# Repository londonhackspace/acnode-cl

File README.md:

Table of Contents
=================

  * [Table of Contents](#table-of-contents)
  * [Features](#features)
  * [Parts list](#parts-list)
    * [For the transistor switch](#for-the-transistor-switch)
    * [For the rest of the node:](#for-the-rest-of-the-node)
    * [Making the transistor switch](#making-the-transistor-switch)
    * [Wiring in the arcade switch](#wiring-in-the-arcade-switch)
    * [How to get this running with a cooqrobot/elechouse pn532 breakout board:](#how-to-get-this-running-with-a-cooqrobotelechouse-pn532-breakout-board)
    * [Using the tool running pin](#using-the-tool-running-pin)
  * [Building and flashing the firmware](#building-and-flashing-the-firmware)
  * [Pin assignments:](#pin-assignments)
  * [using the CLI](#using-the-cli)
  * [Roles](#roles)
  * [Button status/colours:](#button-statuscolours)
  * [To use the button menu:](#to-use-the-button-menu)
    * [For maintainers the menu items are:](#for-maintainers-the-menu-items-are)
    * [So for a user to take a tool out of service:](#so-for-a-user-to-take-a-tool-out-of-service)
    * [For a maintainer to access the menu and do nothing:](#for-a-maintainer-to-access-the-menu-and-do-nothing)
    * [For a maintainer to add a card:](#for-a-maintainer-to-add-a-card)
  * [Glossary](#glossary)
    * [Offline and Online](#offline-and-online)
    * [In service and Out of service](#in-service-and-out-of-service)

# Features

* Command line interface for settings over the usb port

* Stores settings in EEPROM

* Can log to a syslog server

* Uses DHCP to get it's IP address

* Optional pin to detect when a tool is running - good for detecting when consumables are being used

* Can record the total runtime of of the tool if the tool running pin is used.

* Button with RGB led for status.

* Single Button menu for adding cards and putting a tool off and online.

* Can cache 752 cards to the embedded eeprom.

# Parts list

## For the transistor switch

* 1 x NPN transistor, i used a 2N3904
* 1 x 1K resistor
* 1 x small bit (8 x 8 holes is fine) of Vero board
* 2 x C shaped crimp or solderable terminals for the relay
* 2 x wires with female header socket ends (the other end doesn't matter, and will be cut off), one black, and one red.
* 1 x black female to female header socket lead
* 1 x grey female to female header socket lead

## For the rest of the node:

* 2 x crimp or solderable spade terminals for the microswitch on the arcade button
* 2 x wires with female header socket ends (the other end doesn't matter, and will be cut off), one black & one white
* 1 x PN532 based card reader
* 1 x connected Launchpad TM4C1294XL
* 1 x red  female to female header socket lead
* 1 x blue female to female header socket lead
* 1 x green female to female header socket lead
* 1 x black female to female header socket lead

##  Making the transistor switch

* cut one end off the 2 wires with header socket ends, leaving as much wire
as possible and the female ends

* Strip the bare end crimp into the terminals - for the arcade button
terminals use a white and black wire, and for the relay use red and black
wires.

* Attach the red wire to the+ side of the VDC connections on the SSR and the
black one to the - side.

* Attach the red female and to +5v header pin on the launchpad

* On some strip board solder the transistor on one edge with the flat side
facing the rest of the board.

* Cut the track connected to the middle (base) pin of the transistor in the
middle of the board

* Solder the 1K resistor over the hole you've cut

* Solder a 3 pin header so the middle pin goes header -> 1k resistor ->
middle (base) of the transistor, and the left and right pins are connected
to the left and right pin of the transistor

Picture of stripboard + transistor + header:

https://pointless.net/photos/id/1419346624/

Picture of the bottom showing cut track:

https://pointless.net/photos/id/1419346632/

* with the header pins towards you looking edge on at the board (the flat
side of the transistor should be facing you), the pins are, from left to
right:

* 1 connect to GND on the connected launchpad with a black female to female lead.
* 2 connect to PG_1 on the connected launchpad
* 3 connect to - on the ssr VDC side with the black lead you made earlier

## Wiring in the arcade switch

* make two spade terminal leads, one white and one black

like this:

https://pointless.net/photos/id/1419334749/

* connect the black one to the bottom of the microswitch on the button and the other end to a convenient GND on the launchpad

* connect the white end to the terminal labelled "NO" on the microswitch, and the other end to PF_1 on the launchpad

* connect the white lead of the RGB led leads to +5V on the launchpad

* the RGB red, green and blue leads go to PM0, PM1 and PM2

## How to get this running with a cooqrobot/elechouse pn532 breakout board:

1. Cooqrobot boards: Carefully unsolder the 0 ohm resistor jumper from the HIS0 connector, then resolder it (or just bridge the pads with solder) so that the '0' side is connected rather than the 1, this puts the reader in HSU mode.
  Elechouse boards: Set the DIP switches both to the right (This is as shipped from the factory) to put the reader into HSU mode.

2. Solder headers onto the 8 pin connector on the board where the TX/RX pins are, you need at least TX,RX,5V,GND. N.B. Cooqrobot boards: you can't use the SCL/SDA pins on the 4 pin connector because they have pullups on them...

2. Connect 5v and GND to somewhere convenient on the connected launchpad

4. This sketch uses Serial6 which uses PP0 and PP1, AKA pins 43 and 44 on the connected launchpad, connect those too, PP0 goes to TX on the board and PP1 to RX.

5. Check the labels on the card reader boards carefully, one cheap reader board has the pins for the FTDI cable pinouts *backwards* on the top (component) side of the board. Also some card readers label TX and RX the other way round... Do not use cheap Elechouse NFC Reader V3 clones - they often have the wrong component values in their antenna matching stage, and cannot energise cards well. Genuine Elechouse NFC Reader V4 (Direct from Elechouse, work well, the extra price is worth it for avoiding the hassle of deploying an under-performing reader).

See here for the Connected Launchpad pinouts:

http://energia.nu/pin-maps/guide_tm4c129launchpad/

## Using the tool running pin

You can send a signal to the acnode via pin PE_4 to say when your tool is actually running (as opposed to being switched on), useful for keeping track of wear and tear and consumables etc.

# Building and flashing the firmware

(non-PlatformIO version, tested on MacOS 10.12.6, 10.14.4 and Ubuntu 18.04)

* Install git for your platform if you haven't already
* Install cmake for your platform (http://cmake.org , debian/ubuntu package: cmake, MacOS homebrew: `brew install cmake`)
* Create a build directory
```
mkdir build
```
* Run the shell script
```
./gettoolchain.sh
````
* Update/initialise the git submodules
```
git submodule update --init
```
* Use cmake to make a Makefile, and define your target board (EK-TM4C1294XL)
  ```
  cd build && cmake .. -DCMAKE_TOOLCHAIN_FILE=../targets/tivac-launchpad/EK-TM4C1294XL.cmake
  ```
    * If building on MacOS, you may need to put the cmake binary on your path if you downloaded it manually or refer to it as
  /Applications/CMake.app/Contents/bin/cmake
* Use Gnu make to actually run the dependencies, compile and link:
```
make -j
```
* When ready to upload the resultant elf binary to the Launchpad,
```
make -j flash
```

# Pin assignments:

* PG_1 - active high, switches power to the tool, output
* PF_1 - the button, active low (uses internal pullup), input
* PM_0 - RGB button Red channel, output
* PM_1 - RGB button Green channel, output
* PM_2 - RGB button Blue channel, output
* PP_0 - Serial RX from the card reader, input (should connect to TX on the card reader)
* PP_1 - Serial TX to the card reader, output (should connect to RX on the card reader)
* PE_4 - tool running pin, active low (uses internal pullup), input
* PD_0 - SD Card MISO (pin 7) aka D0
* PD_1 - SD Card MOSI (pin 2) aka CMD
* PD_3 - SD card clock (pin 5)
* PC_7 - SD card CS (pin 1) aka CD

# Pin assignments on ACNode shield rev 1 board (square PCB)

Other ACnode PCBs are available, the most common at the moment is the hardware/NEW-ACNode-Dootbot-Shield designed by dawidekziaja

* P1 connector (numbers rising towards on-board relay, P1_1 is furthest from it)
* P1_1 GND -> CAT5 ORANGE
* P1_2 +3.3V    NOT CONNECTED
* P1_3 PP0 RX ->  CAT5 WHITE/GREEN -> PN532 TXD
* P1_4 PP1 TX -> CAT5 GREEN -> PN532 RXD

* P3 connector (numbers rising towards reset button)
* P3_1 +3.3V
* P3_2 Red LED -> CAT5 BLUE
* P3_3 Green LED -> CAT5 WHITE/BROWN
* P3_4 Blue LED -> CAT5 BROWN

* P4 connector (numbers rising away from reset button)
* P4_1 +5V -> CAT5 WHITE/ORANGE
* P4_2 
* P4_3 GND

Button connector / Doorbell or ACnode menu button
* PF_1 SWITCH -> CAT5 WHTE/BLUE
* GND 

Door release button
* PM6 SWITCH -> Normally Open
* GND

* Note that Deek-Robot and Elechouse branded PN532 boards need +5V not +3.3v to function. 
Use the pinouts labelled on the back of the board.
Other boards (Genuine Elechouse NFC module v3) sort of work at +3.3V, but may not give sufficient juice to the NFC target to energise certain types of cards.

# Reader installation

For convenience of installation (acnode), and added security (doorbot), we recommend the reader module itself should be connected via an 8 wire cable, such as CAT5, and housed with a push-button NO switch and RGB LED in its own enclosure. This way, any intruder can't attack the reader and easily gain access. CAT5 (or above) wiring as above. Note the requirement for 220 ohm resistors on the Red/Green/Blue LED pins to prevent LED burnout. For operational convenience, it is advised to keep a spare reader that can be swapped out. Readers for doorbot enclosures can fit into standard single EN 60670-1 socket boxes with blanking plates, or outdoor junction boxes. For outdoor fitting, ensure that any holes for the button are suitably sealed against moisture ingress. Ditto for ACnode readers in a dusty or dirty environment. 

# Common reader enclosures

## ACnode role
Schneider Electric P/N SL00925 100x100x500 junction box smooth walls has been used for ACnode enclosures in the past. (Farnell DPN10/10 161706)
[ Internal free space 80x80x35mm to brim, there's 10mm outside of this area, compromised by the  mounting posts for the cover ]
[ Cover free space 80x80x16mm to brim, there's 10mm outside of this area, compromised by the mounting posts for the cover ]
Arcade Button with 5V Common Cathode RGB LED, from https://www.arcadeworlduk.com/, e.g. Ultralux RGB Illuminated Arcade Button, mounting hole required 28mm diameter hole in side of enclosure.
Mount PN532 reader and breakout board on the lid
(Optional - use RJ45 modular jack on the side of the enclosure and run a small patch lead to the breakout board, or find a suitable way of terminating the CAT5). Ideally, the readers are easily swappable between ACnodes, so mod jack on the side is a good plan.
Mount modular jack on opposite side of enclosure box to arcade button.

## Internal doorbot role

BS EN 60670-1 45mm deep single socket box with blanking plate
5V Common Cathode RGB LED
N/O SPST push button for doorbell. Choose one that doesn't accidentally get triggered while swiping.
Mount PN532 reader and breakout board on the blanking plate. Wire RJ45 CAT5 cable within walls.
## External doorbot role

British General WPJBS IP55 external junction box from B&Q
[ Internal free space 50x60x35mm, 8mm outide this space, compromised by the mounting posts for the cover ]
5V Common Cathode RGB LED
N/O SPST push button, *water resistant*. Choose one that doesn't accidentally get triggered while swiping.
Run CAT5 cable through a sealed grommet on the rear through the wall.

Pin Assignments
* +5V : RJ45_1 : WHITE/ORANGE : +5V
* GND : RJ45_2 : ORANGE : GND
* PP_0 : RJ45_3 : WHITE/GREEN : -> PN532 TXD
* PM_0 : RJ45_4 : BLUE : VIA R220 - RGB RED 
* PF_1 : RJ45_5 : WHITE/BLUE : the button, active low (uses internal pullup), input
* PP_1 : RJ45_6 : GREEN : PN532 RXD
* PM_1 : RJ45_7 : WHITE/BROWN : VIA R220 - RGB Green
* PM_2 : RJ45_8 : BROWN : VIA R220 - RGB BLUE

# Power supply

For ACnodes, then a Power over Ethernet micro-USB power splitter works a treat. Feed the 5V USB power straight to the OTG micro USB connector near the ethernet jack, and jumper the Power Select to OTG. Make sure you connect to a network port that is supplied via a PoE network switch.
For doorbots, you will need +12V to power the door solenoid, and ideally, a battery backup. Feed the +12V into the London Hackspace doorbot board so that it goes via a regulator to supply +5V to the Launchpad via the BoosterPack connector. Jumper the launchpad's Power Select to OTG.

# using the CLI

Once the firmware has been uploaded to the connected launchpad connect with a serial terminal (if you use a real one rather than the Energia serial monitor you get command history and line editing).
It will work a lot better if it's connected to a working ethernet port with DHCP at this point.

Use `help` to see a brief description of commands. You want to set the nodeid and toolname as the minimum:

```
nodeid <id>
name <name of tool>
server <acserver hostname>
port <http port to use>
secret <shared secret, see acserver tool config>
syslog <syslog server to use>
mqtt_topic_base <mqtt_topic_base e.g. /tool/selfclearingdesk >
maintainercache - toggle maintainer cache mode (stores maintainers credentials in EEPROM so it should still work for maintainers after complete power loss)
```

and then `save` to save the settings.

It is good practice to make a note of the MAC address of the acnode, and reserve a DHCP reservation on the router for it, because then it can be monitored by icinga or other monitoring system.

# Button status/colours:

* Starting up: rainbow cycling
* In service, idle: blue
* In service, valid user, tool on: green
* In service, invalid user: red
* In service, maintainer: yellow
* Out of service, idle: flashing blue/red
* Out of service, valid user: red (and the tool will be off)
* Out of service, maintainer: yellow (and the tool will turn on)
* Doorbell pressed: Long Orange / Blue / Orange / Blue
* Door released: Green
* Door access denied: Red

# Roles

Each node can work in a variety of roles:

## Regular ACNode (0)

Provided that a card known to the system is presented, and it has access to this particular tool, the relay is active
as long as the card is on the reader.

## Doorbot (1)

Provided that a card known to the system is presented, the relay is activated for `KEEP_OPEN_MILISECONDS` (1.5 seconds).

## Doorbot with access control (2)

Provided that a card known to the system is presented, and it has access to this particular tool (door), the relay
is activated for `KEEP_OPEN_MILISECONDS` (1.5 seconds).

## Audit only (3)

Provided that a card known to the system is presented, the relay is active as long as the card is on the reader.
This is used primarily for logging what user was using a tool at what time.

# To use the button menu:

A short press starts the menu and switches between items, a long press selects a menu item.

For users the only menu item is to take the tool out of service - it's flashing red/green

The menu also times out after 60 seconds.

## For maintainers the menu items are:

* Add a user (flashing Amber)
* Take the tool out of service (if it's in service) - flashing red
* put a tool in service (if it's out of service), flashing green.

## So for a user to take a tool out of service:

* Press the button once, quickly, the button will be flashing red/green.
* Hold the button down for a second or so and release.

The button will go solid red and the tool will be out of service

## For a maintainer to access the menu and do nothing:

* Press the button once, the button will flash Amber/yellow - the ACNode is in add mode.
* Press the button again, the button will flash red/yellow - the menu is in take tool out of service mode.
* Press the button again, the button will stop flashing, you have exited the menu.

## For a maintainer to add a card:

* Press the button, it will flash Amber/yellow
* Press the button for 1 second or so and let it go, the button will go yellow
* Remove the maintainer card. add the card to be added - the button will go orange (invalid card colour)
* Remove the card.

The new card should now be added.

# Glossary

## Offline and Online

The tool does not (or does) have a working network connection to the acserver. Things that can make an ACNode offline include:

* network cable unplugged
* Ethernet switch powered off or dead
* DHCP server down
* dns server down
* acserver VM down
* acserver VM running, but no acserver running
* acserver running, but crashing or having problems (e.g. database down, no cards in database)

## Nice to have services

The list of dependencies that are nice to have, but not strictly necessary

* mqtt server should be up, if announce_mode is set to mqtt (now default on new installs)

## In service and Out of service

Manually set by a maintainer or user - users can set a tool out of service, only a maintainer can put a tool in service, in/out of service state is kept in the acserver database and on the ACNode it's self
In doorbot or doorbot access control roles, in-service or out of service has no meaning, and has no way of setting this state, other than via the acserver itself.

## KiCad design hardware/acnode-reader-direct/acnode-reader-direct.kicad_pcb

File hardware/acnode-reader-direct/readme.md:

# AC node / doorbot breakout board
rev 1.1a

Designed in kicad 6

designed to connect an RJ45 socket to an Elechouse V4 NFC module
without spaghetti wiring.

Inspired by Liam's solder-pad version.

Initial revision of this is targeted at EN 60670-1 socket back-boxes / blanking plate builds as used by Doorbots.
There's no reason not to use them for acnodes as well, but a near-future revision (possibly before ordering the boards)
will include support for the existing boxes used for AC node builds with the massive arcade buttons, by means of different
mounting holes.

# Errata

rev 1.1: J2 RGB LED silkscreen is labelled backwards. Should read B- G- +5 R-, with R- closest to the middle of the board, corrected in rev 1.1a

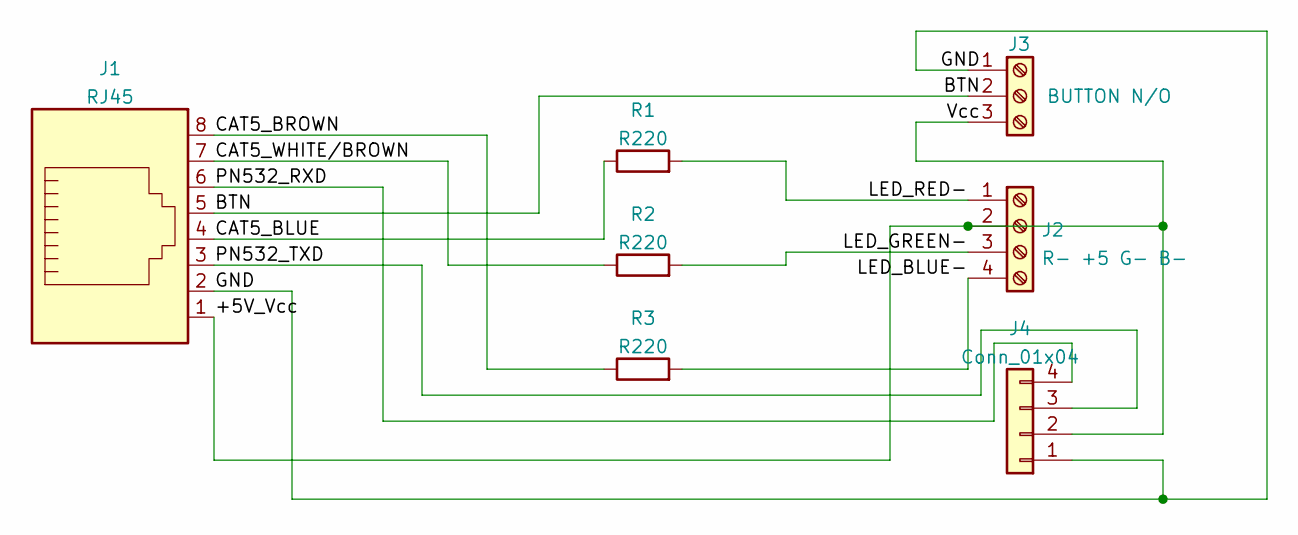
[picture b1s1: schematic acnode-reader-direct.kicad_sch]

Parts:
J1: RJ45; RJ45_Amphenol_RJHSE5380
J2: R- +5 G- B-; TerminalBlock_TE_282834-4_1x04_P2.54mm_Horizontal
J3: BUTTON N/O; TerminalBlock_TE_282834-2_1x02_P2.54mm_Horizontal
J4: Conn_01x04; PinSocket_1x04_P2.54mm_Horizontal
R1, R2, R3: R220; R_Axial_DIN0309_L9.0mm_D3.2mm_P12.70mm_Horizontal

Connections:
/+5V_Vcc: J1.1, J2.2, J3.3, J4.2
/BTN: J1.5, J3.2
/CAT5_BLUE: J1.4, R1.1
/CAT5_BROWN: J1.8, R3.1
/CAT5_WHITE/BROWN: J1.7, R2.1
/GND: J1.2, J3.1, J4.1
/LED_BLUE-: J2.4, R3.2
/LED_GREEN-: J2.3, R2.2
/LED_RED-: J2.1, R1.2
/PN532_RXD: J1.6, J4.4
/PN532_TXD: J1.3, J4.3

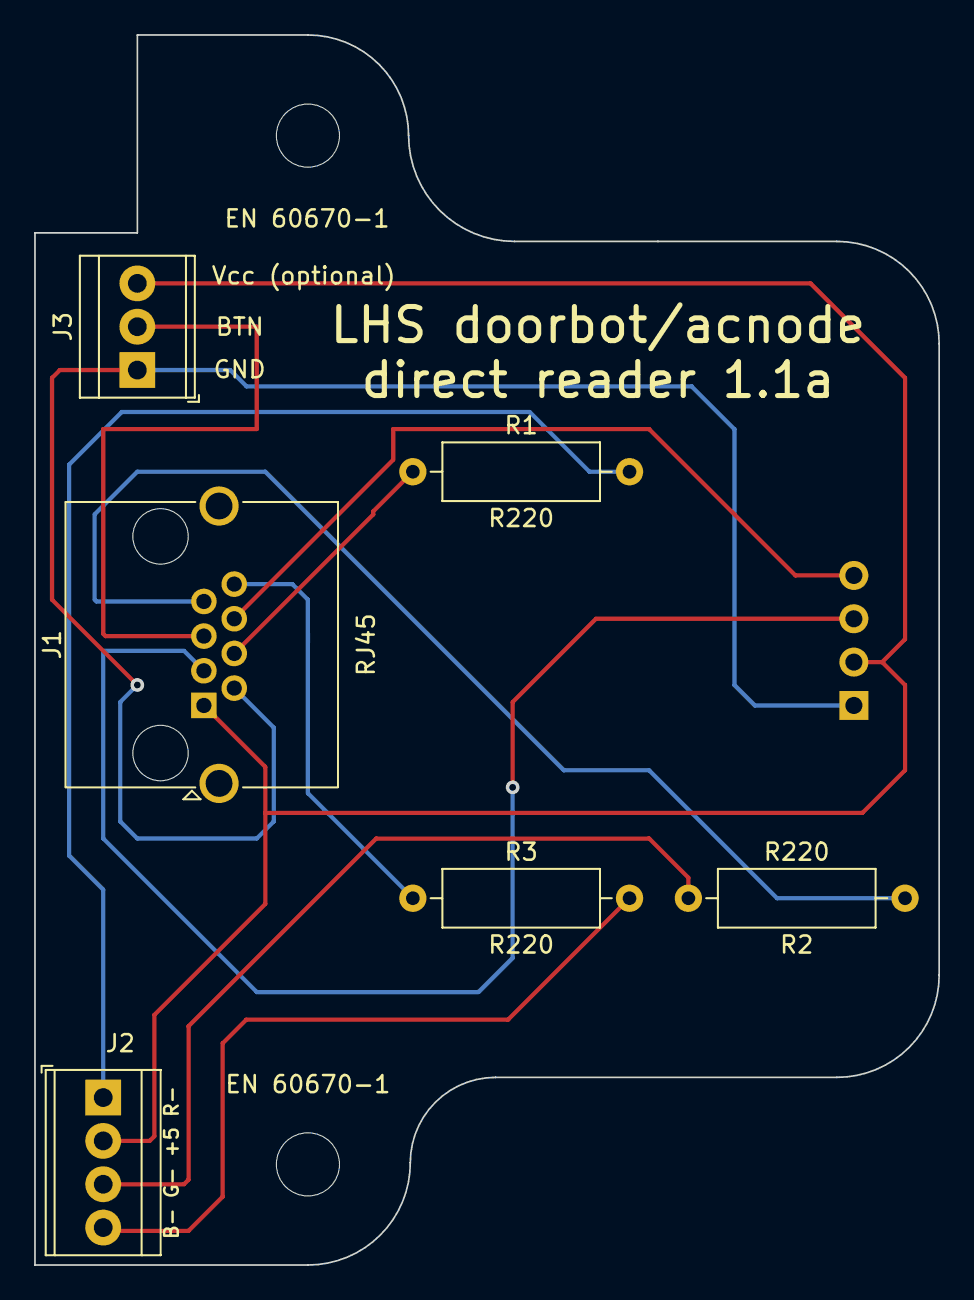
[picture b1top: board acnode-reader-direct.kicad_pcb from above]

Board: 2 copper layers, 53.0 x 72.1 mm, 9 parts (1 on the bottom side), 11 nets.

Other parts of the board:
EN 60670-1, EN 60670-1#2: MountingHole_3.7mm

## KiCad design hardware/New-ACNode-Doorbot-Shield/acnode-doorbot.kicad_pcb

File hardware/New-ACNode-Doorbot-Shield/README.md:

# acnode-doorbot
A board designed to be used for ACNode and Doorbot at London Hackspace
# Board View and 3D Render

# Errata
rev 1.1 : RJ45 connector is round the wrong way
rev 1.1a : Relay outputs silkscreen is labelled incorrectly. NC is actually on the side closest to the SD card connector, not the voltage regulator side which is NO.

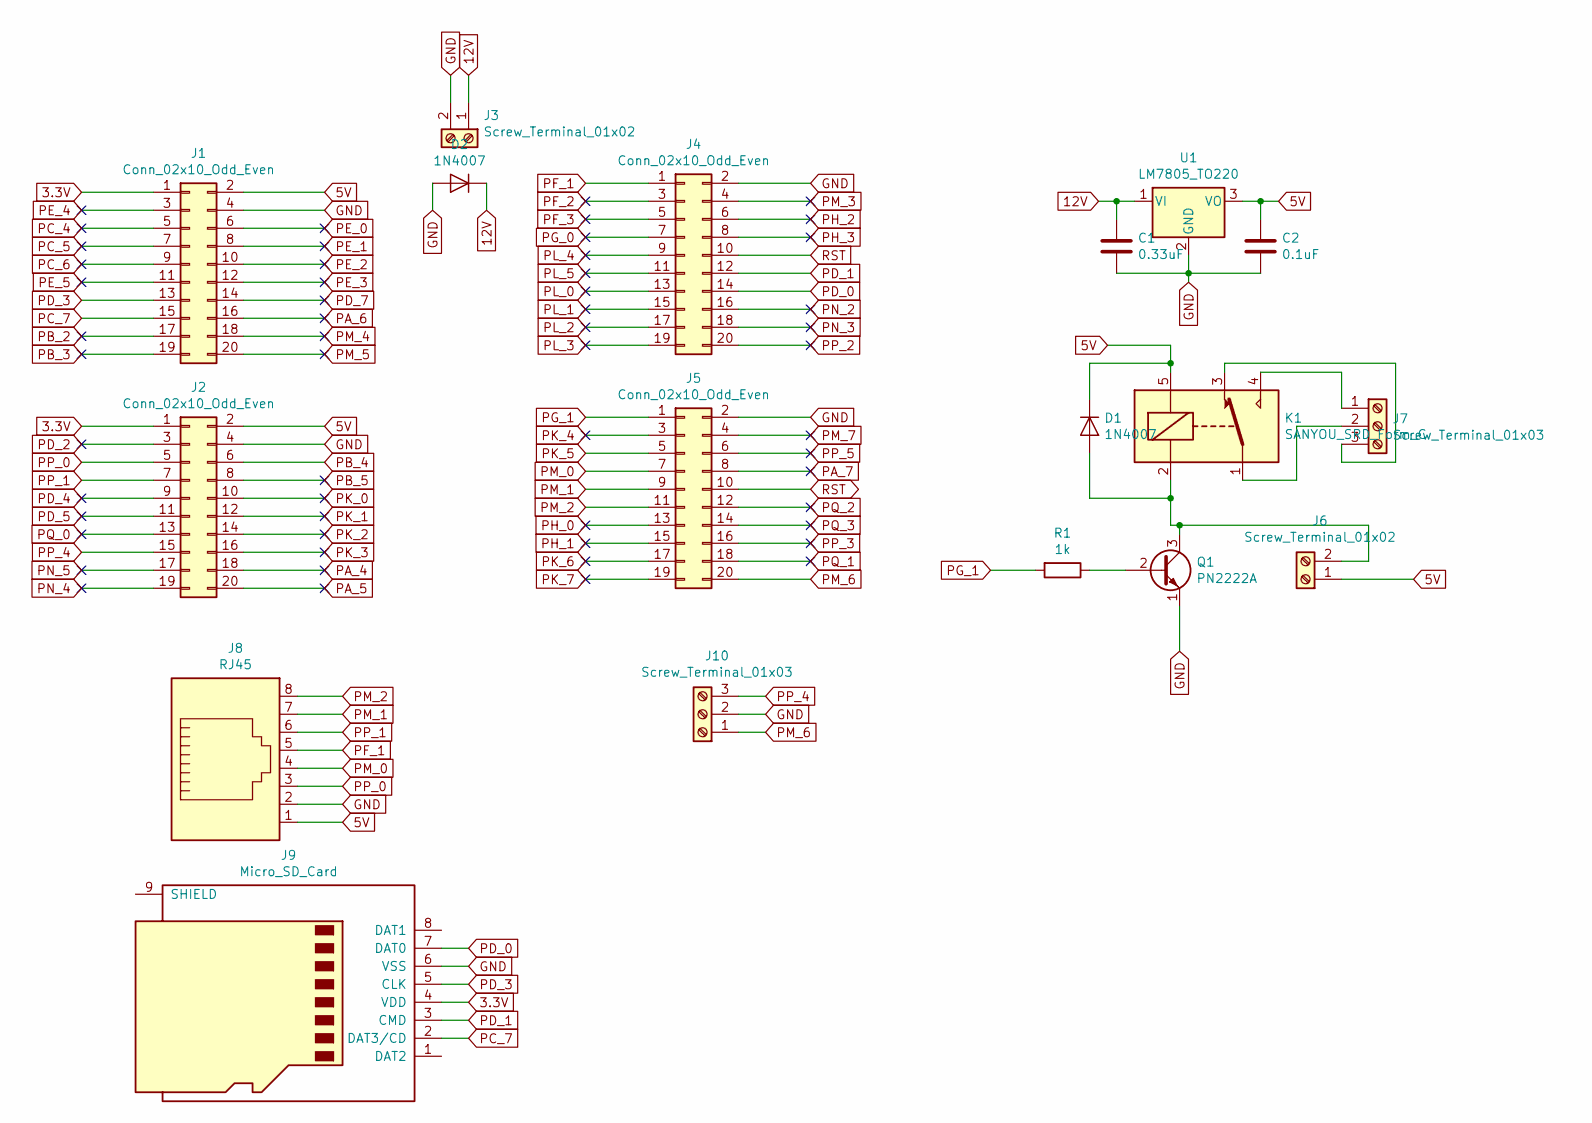
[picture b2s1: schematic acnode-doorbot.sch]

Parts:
C1: 0.33uF; C_Disc_D5.0mm_W2.5mm_P2.50mm
C2: 0.1uF; C_Disc_D5.0mm_W2.5mm_P2.50mm
D1, D2: 1N4007; D_DO-41_SOD81_P10.16mm_Horizontal
J1, J2, J4, J5: Conn_02x10_Odd_Even; PinHeader_2x10_P2.54mm_Vertical
J3: Screw_Terminal_01x02; TerminalBlock_Phoenix_MKDS-3-2-5.08_1x02_P5.08mm_Horizontal
J6: Screw_Terminal_01x02; TerminalBlock_Phoenix_MPT-0,5-2-2.54_1x02_P2.54mm_Horizontal
J7: Screw_Terminal_01x03; TerminalBlock_RND_205-00288_1x03_P5.08mm_Horizontal
J8: RJ45; RJ45_Amphenol_RJHSE5380
J9: Micro_SD_Card; microSD_HC_Wuerth_693072010801
J10: Screw_Terminal_01x03; TerminalBlock_TE_282834-3_1x03_P2.54mm_Horizontal
K1: SANYOU_SRD_Form_C; Relay_SPDT_SANYOU_SRD_Series_Form_C
Q1: PN2222A; TO-92_Inline
R1: 1k; R_Axial_DIN0207_L6.3mm_D2.5mm_P10.16mm_Horizontal
U1: LM7805_TO220; TO-220-3_Vertical

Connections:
3.3V: J1.1, J2.1, J9.4 (VDD)
5V: C2.1, D1.1 (K), J1.2, J2.2, J6.1, J8.1, K1.5, U1.3 (VO)
12V: C1.1, D2.1 (K), J3.1, U1.1 (VI)
GND: C1.2, C2.2, D2.2 (A), J1.4, J2.4, J3.2, J4.2, J5.2, J8.2, J9.6 (VSS), J10.2, Q1.1 (E), U1.2 (GND)
unnamed: D1.2 (A), J6.2, K1.2, Q1.3 (C)
unnamed: J7.1, K1.4
unnamed: J7.2, K1.1
unnamed: J7.3, K1.3
unnamed: Q1.2 (B), R1.1
PA_4: J2.18
PA_5: J2.20
PA_6: J1.16
PA_7: J5.8
PB_2: J1.17
PB_3: J1.19
PB_4: J2.6
PB_5: J2.8
PC_4: J1.5
PC_5: J1.7
PC_6: J1.9
PC_7: J1.15, J9.2 (DAT3/CD)
PD_0: J4.14, J9.7 (DAT0)
PD_1: J4.12, J9.3 (CMD)
PD_2: J2.3
PD_3: J1.13, J9.5 (CLK)
PD_4: J2.9
PD_5: J2.11
PD_7: J1.14
PE_0: J1.6
PE_1: J1.8
PE_2: J1.10
PE_3: J1.12
PE_4: J1.3
PE_5: J1.11
PF_1: J4.1, J8.5
PF_2: J4.3
PF_3: J4.5
PG_0: J4.7
PG_1: J5.1, R1.2
PH_0: J5.13
PH_1: J5.15
PH_2: J4.6
PH_3: J4.8
PK_0: J2.10
PK_1: J2.12
PK_2: J2.14
PK_3: J2.16
PK_4: J5.3
PK_5: J5.5
PK_6: J5.17
PK_7: J5.19
PL_0: J4.13
PL_1: J4.15
PL_2: J4.17
PL_3: J4.19
PL_4: J4.9
PL_5: J4.11
PM_0: J5.7, J8.4
PM_1: J5.9, J8.7
PM_2: J5.11, J8.8
PM_3: J4.4
PM_4: J1.18
PM_5: J1.20
PM_6: J5.20, J10.1
PM_7: J5.4
PN_2: J4.16
PN_3: J4.18
PN_4: J2.19
PN_5: J2.17
PP_0: J2.5, J8.3
PP_1: J2.7, J8.6
PP_2: J4.20
PP_3: J5.16
PP_4: J2.15, J10.3
PP_5: J5.6
PQ_0: J2.13
PQ_1: J5.18
PQ_2: J5.12
PQ_3: J5.14
RST: J4.10, J5.10

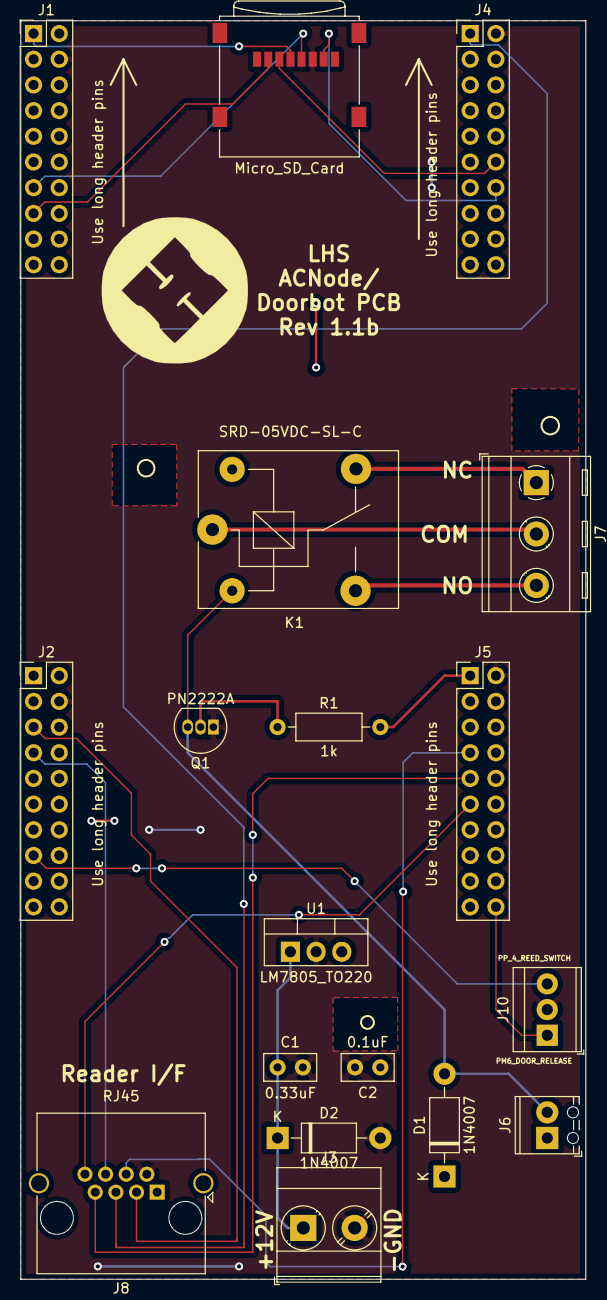
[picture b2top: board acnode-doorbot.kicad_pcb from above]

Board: 2 copper layers, 55.9 x 124.5 mm, 18 parts (0 on the bottom side), 23 nets.

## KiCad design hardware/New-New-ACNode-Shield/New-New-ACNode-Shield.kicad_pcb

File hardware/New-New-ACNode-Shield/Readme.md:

This is yet another board. IT IS NOT YET READY FOR USE!

It's basically a backport of the design I came up with for a Nucleo-based version. Key features include:
* An LED on the board for debugging
* A button on the board for debugging
* Support for RS-422 reader connection
* SPI Flash instead of SD Card
* Opto-isolated tool on input
* Trasistor-buffered door release with ferrite beads

Things to fix before the next version:

* Launchpad ethernet connector fouls the shield
* LED is... rather bright...
* A jumper on the ISL3176 ~RE line would allow a single board to support 5V and 12V readers
* Footprints for 3.81mm connectors are too tight - holes too small

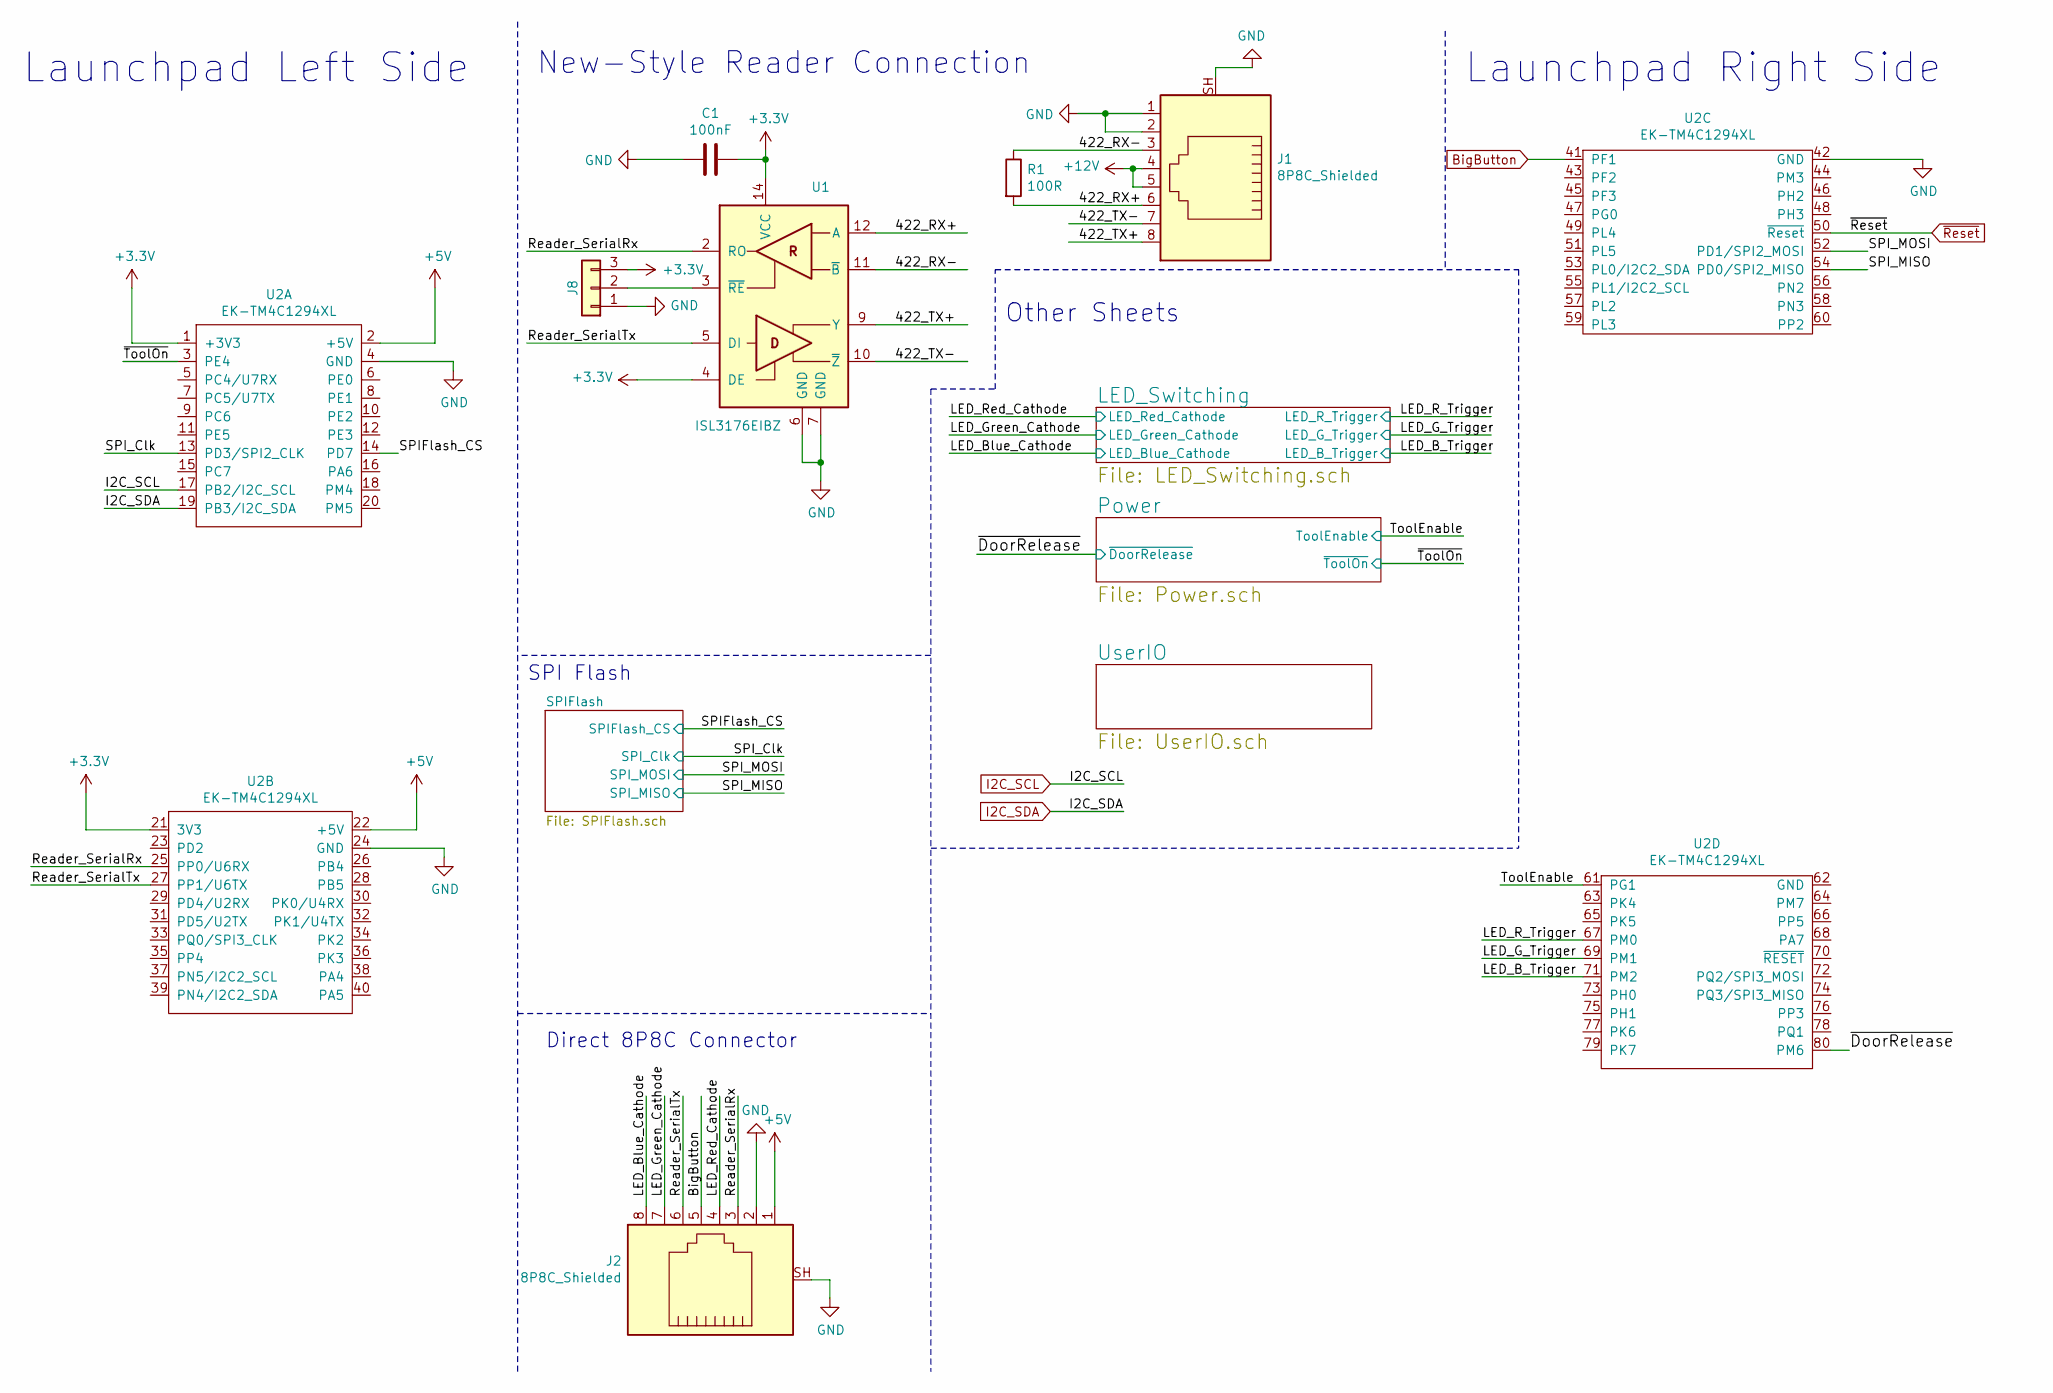
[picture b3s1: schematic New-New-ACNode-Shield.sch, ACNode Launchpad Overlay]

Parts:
C1: 100nF; C_0603_1608Metric
J1, J2: 8P8C_Shielded; RJ45_Ninigi_GE
J8: Conn_01x03; PinHeader_1x03_P2.54mm_Vertical
R1: 100R; R_0603_1608Metric
U1: ISL3176EIBZ; SOIC-14_3.9x8.7mm_P1.27mm
U2: EK-TM4C1294XL; Launchpad

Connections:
+3V3: C1.1, J8.3, U1.4 (DE), U1.14 (VCC), U2.1 (+3V3), U2.21 (3V3); also elsewhere on the board
+5V: J2.1, U2.2 (+5V), U2.22 (+5V); also elsewhere on the board
+12V: J1.4, J1.5; also elsewhere on the board
/422_RX+: J1.6, R1.2, U1.12 (A)
/422_RX-: J1.3, R1.1, U1.11 (~B)
/422_TX+: J1.8, U1.9 (Y)
/422_TX-: J1.7, U1.10 (~Z~)
/LED_B_Trigger: U2.71 (PM2); also elsewhere on the board
/LED_Blue_Cathode: J2.8; also elsewhere on the board
/LED_G_Trigger: U2.69 (PM1); also elsewhere on the board
/LED_Green_Cathode: J2.7; also elsewhere on the board
/LED_R_Trigger: U2.67 (PM0); also elsewhere on the board
/LED_Red_Cathode: J2.4; also elsewhere on the board
/Reader_SerialRx: J2.3, U1.2 (RO), U2.25 (PP0/U6RX)
/Reader_SerialTx: J2.6, U1.5 (DI), U2.27 (PP1/U6TX)
/SPIFlash_CS: U2.14 (PD7); also elsewhere on the board
/SPI_Clk: U2.13 (PD3/SPI2_CLK); also elsewhere on the board
/SPI_MISO: U2.54 (PD0/SPI2_MISO); also elsewhere on the board
/SPI_MOSI: U2.52 (PD1/SPI2_MOSI); also elsewhere on the board
/ToolEnable: U2.61 (PG1); also elsewhere on the board
/~DoorRelease: U2.80 (PM6); also elsewhere on the board
/~ToolOn: U2.3 (PE4); also elsewhere on the board
BigButton: J2.5, U2.41 (PF1); also elsewhere on the board
GND: C1.2, J1.1, J1.2, J1.SH, J2.2, J2.SH, J8.1, U1.6 (GND), U1.7 (GND), U2.4 (GND), U2.24 (GND), U2.42 (GND); also elsewhere on the board
I2C_SCL: U2.17 (PB2/I2C_SCL); also elsewhere on the board
I2C_SDA: U2.19 (PB3/I2C_SDA); also elsewhere on the board
unnamed: J8.2, U1.3 (~RE)
~Reset: U2.50 (~Reset); also elsewhere on the board

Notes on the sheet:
Launchpad Left Side
Launchpad Right Side
Direct 8P8C Connector
SPI Flash
New-Style Reader Connection
Other Sheets

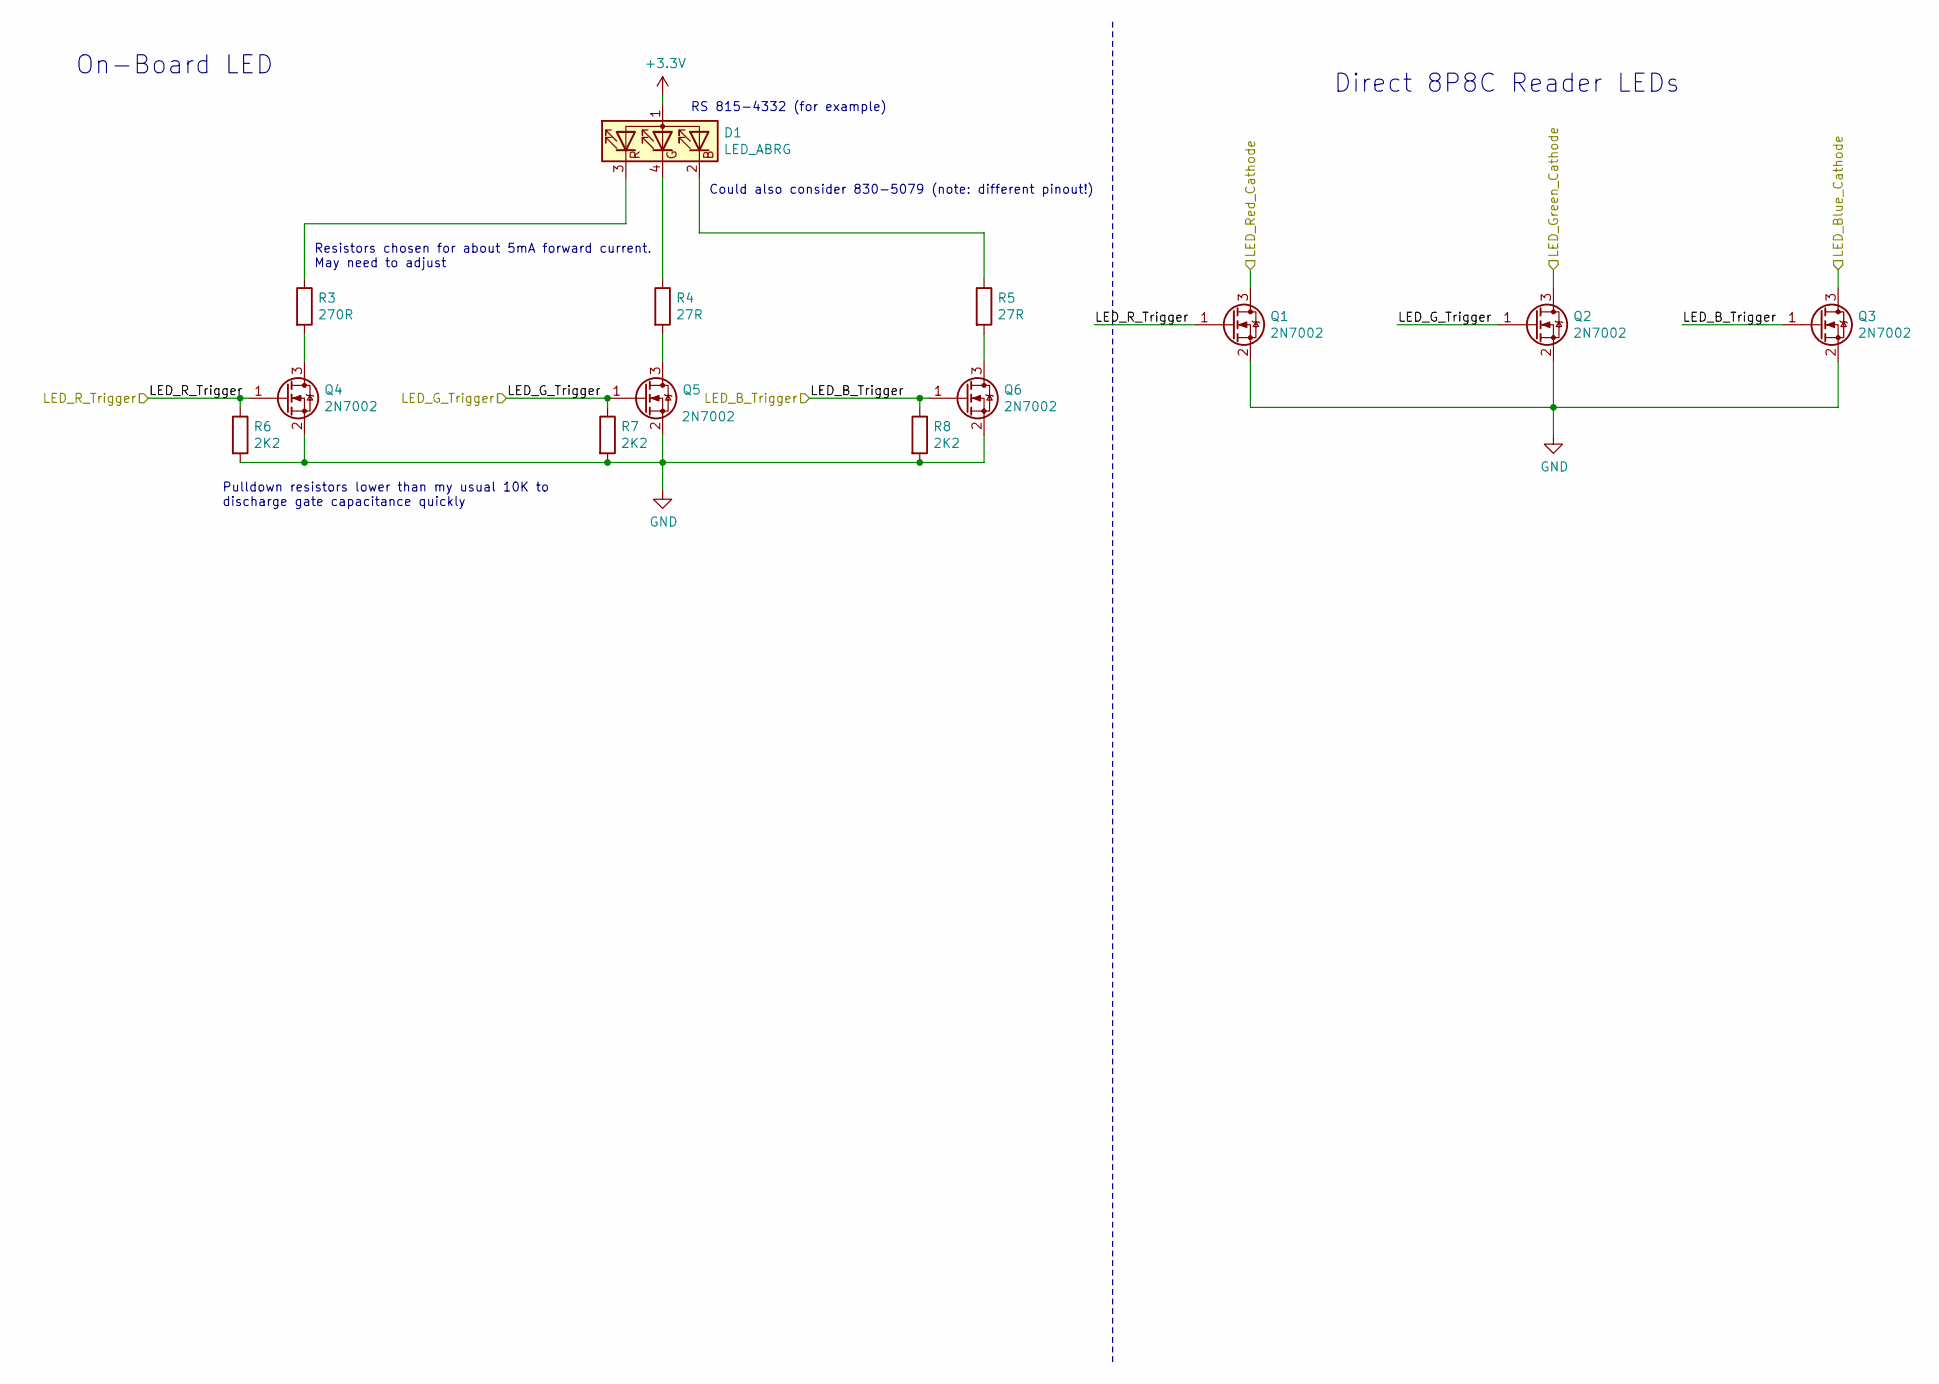
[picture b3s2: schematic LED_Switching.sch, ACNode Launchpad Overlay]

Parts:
D1: LED_ABRG; Wurth_3528_LED
Q1, Q2, Q3, Q4, Q5, Q6: 2N7002; SOT-23
R3: 270R; R_0603_1608Metric
R4, R5: 27R; R_0603_1608Metric
R6, R7, R8: 2K2; R_0603_1608Metric

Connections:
+3V3: D1.1 (A); also elsewhere on the board
/LED_B_Trigger: Q3.1 (G), Q6.1 (G), R8.1; also elsewhere on the board
/LED_Blue_Cathode: Q3.3 (D); also elsewhere on the board
/LED_G_Trigger: Q2.1 (G), Q5.1 (G), R7.1; also elsewhere on the board
/LED_Green_Cathode: Q2.3 (D); also elsewhere on the board
/LED_R_Trigger: Q1.1 (G), Q4.1 (G), R6.1; also elsewhere on the board
/LED_Red_Cathode: Q1.3 (D); also elsewhere on the board
GND: Q1.2 (S), Q2.2 (S), Q3.2 (S), Q4.2 (S), Q5.2 (S), Q6.2 (S), R6.2, R7.2, R8.2; also elsewhere on the board
unnamed: D1.2 (BK), R5.1
unnamed: D1.3 (RK), R3.1
unnamed: D1.4 (GK), R4.1
unnamed: Q4.3 (D), R3.2
unnamed: Q5.3 (D), R4.2
unnamed: Q6.3 (D), R5.2

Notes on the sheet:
RS 815-4332 (for example)
On-Board LED
Direct 8P8C Reader LEDs
Pulldown resistors lower than my usual 10K to discharge gate capacitance quickly
Could also consider 830-5079 (note: different pinout!)
Resistors chosen for about 5mA forward current. May need to adjust

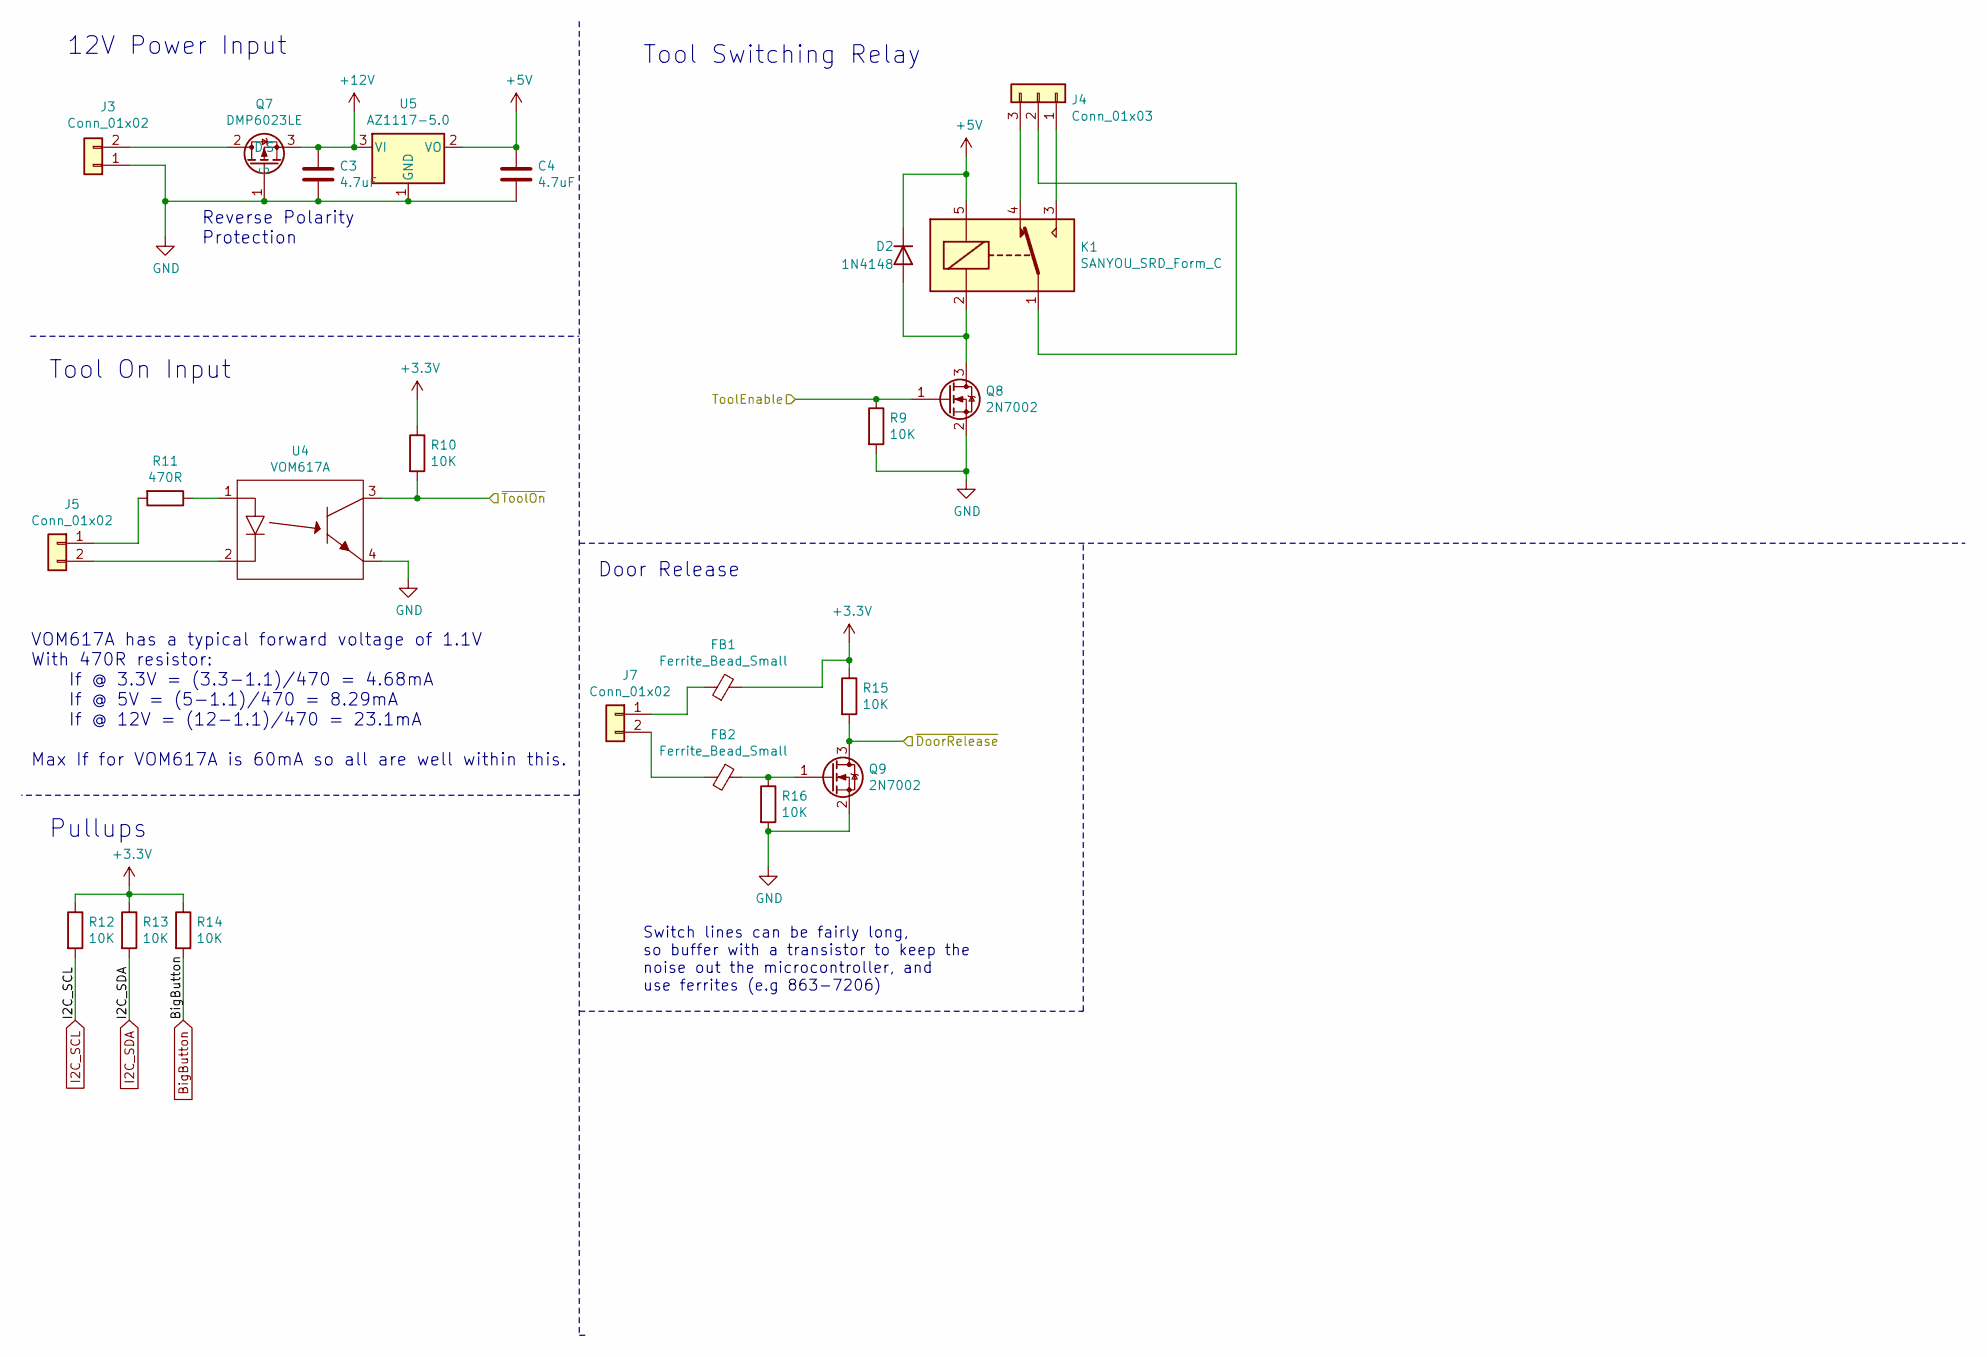
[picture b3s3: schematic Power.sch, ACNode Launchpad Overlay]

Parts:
C3, C4: 4.7uF; C_0805_2012Metric
D2: 1N4148; D_DO-35_SOD27_P7.62mm_Horizontal
FB1, FB2: Ferrite_Bead_Small; C_0805_2012Metric
J3: Conn_01x02; Connector-5.08mm
J4: Conn_01x03; Connector-3.81mm-3pin
J5, J7: Conn_01x02; Connector-3.81mm-2pin
K1: SANYOU_SRD_Form_C; Relay_SPDT_SANYOU_SRD_Series_Form_C
Q7: DMP6023LE; SOT-223
Q8, Q9: 2N7002; SOT-23
R9, R10, R12, R13, R14, R15, R16: 10K; R_0603_1608Metric
R11: 470R; R_0603_1608Metric
U4: VOM617A; VOM617A-4SOP
U5: AZ1117-5.0; SOT-223-3_TabPin2

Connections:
+3V3: FB1.2, R10.1, R12.1, R13.1, R14.1, R15.1; also elsewhere on the board
+5V: C4.1, D2.1 (K), K1.5, U5.2 (VO); also elsewhere on the board
+12V: C3.1, Q7.3 (S), U5.3 (VI); also elsewhere on the board
/ToolEnable: Q8.1 (G), R9.1; also elsewhere on the board
/~DoorRelease: Q9.3 (D), R15.2; also elsewhere on the board
/~ToolOn: R10.2, U4.3; also elsewhere on the board
BigButton: R14.2; also elsewhere on the board
GND: C3.2, C4.2, J3.1, Q7.1 (G), Q8.2 (S), Q9.2 (S), R9.2, R16.2, U4.4, U5.1 (GND); also elsewhere on the board
I2C_SCL: R12.2; also elsewhere on the board
I2C_SDA: R13.2; also elsewhere on the board
unnamed: D2.2 (A), K1.2, Q8.3 (D)
unnamed: FB1.1, J7.1
unnamed: FB2.1, Q9.1 (G), R16.1
unnamed: FB2.2, J7.2
unnamed: J3.2, Q7.2 (D), Q7.4 (Tab)
unnamed: J4.1, K1.3
unnamed: J4.2, K1.1
unnamed: J4.3, K1.4
unnamed: J5.1, R11.2
unnamed: J5.2, U4.2
unnamed: R11.1, U4.1

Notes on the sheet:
Reverse Polarity Protection
12V Power Input
Tool Switching Relay
Tool On Input
VOM617A has a typical forward voltage of 1.1V With 470R resistor: If @ 3.3V = (3.3-1.1)/470 = 4.68mA If @ 5V = (5-1.1)/470 = 8.29mA If @ 12V = (12-1.1)/470 = 23.1mA Max If for VOM617A is 60mA so all are well within this.
Pullups
Door Release
Switch lines can be fairly long, so buffer with a transistor to keep the noise out the microcontroller, and use ferrites (e.g 863-7206)
